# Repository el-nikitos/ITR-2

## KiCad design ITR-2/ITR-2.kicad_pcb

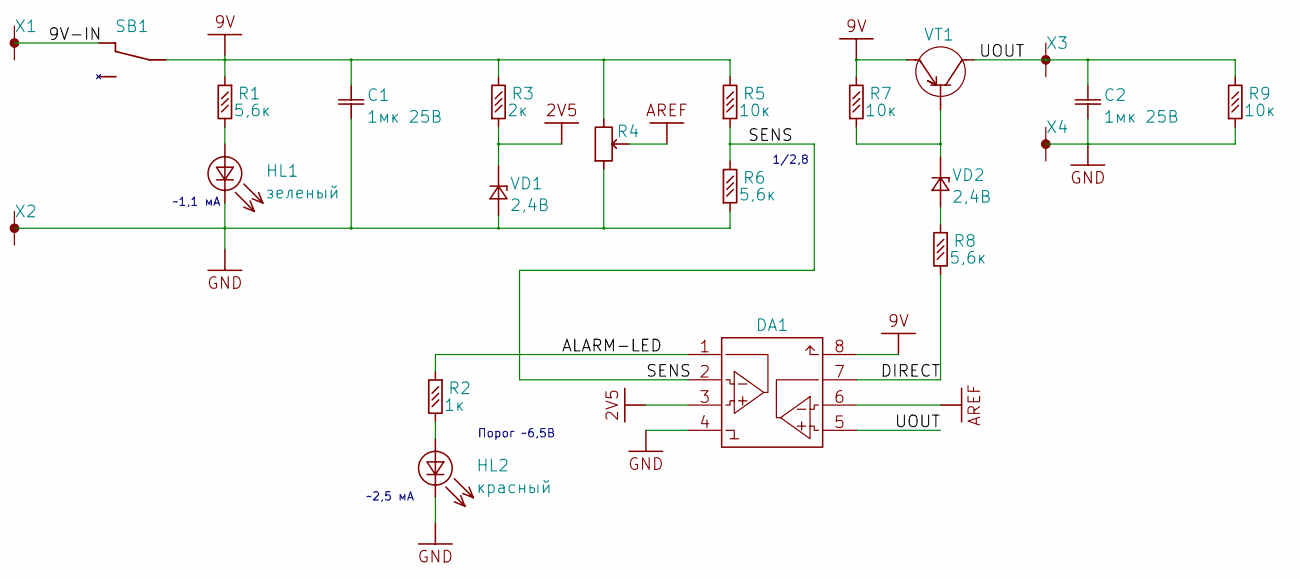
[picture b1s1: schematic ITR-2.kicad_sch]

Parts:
C1, C2: smd-конденсатор-керамика*0,01мк*25В*0603*ВП; Конденсатор_SMD_IEC_0603
DA1: ОУ*сдвоенный*so-8*ОТК; SO-8
HL1: smd-светодиод*зеленый*10мА*0603*ВП; Светодиод_SMD_IEC_0603(AK)
HL2: smd-светодиод*красный*10мА*0603*ВП; Светодиод_SMD_IEC_0603(AK)
R1, R2, R8: smd-резистор*4,7к*0603*ВП; Резистор_SMD_IEC_0603-0,1_Вт
R3, R5, R6, R7, R9: smd-резистор*10к*0,1Вт*5проц*0603*ВП; Резистор_SMD_IEC_0603-0,1_Вт
R4: DIP-переменный_резистор_R1001N12B1-A10K_вертикаль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; R1001N12B1-A10K-vertical
SB1: DIP-переключатель_KLS7-SS-12F19-G5; KLS7-SS-12F19-G5
VD1, VD2: smd-стабилитрон*6,8В*5мА*КД-36*ОТК; Корпус_IEC_КД-36
VT1: smd-транзистор*pnp*0,5А*50В*КТ-46*ОТК; Корпус_КТ-46
X1, X2, X3, X4: ico*группа_монтажных_отв.&1шт_1.2мм; Отверстие_под_пайку_D1.2

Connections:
2V5: DA1.3, R3.1, VD1.K
9V: C1.2, DA1.8, R1.1, R3.2, R4.3, R5.2, R7.2, SB1.2, VT1.2
/9V-IN: SB1.1, X1.1
/ALARM-LED: DA1.1, R2.1
/DIRECT: DA1.7, R8.2
/SENS: DA1.2, R5.1, R6.2
/UOUT: C2.2, DA1.5, R9.2, VT1.3, X3.1
AREF: DA1.6, R4.2
GND: C1.1, C2.1, DA1.4, HL1.K, HL2.K, R4.1, R6.1, R9.1, VD1.A, X2.1, X4.1
unnamed: HL1.A, R1.2
unnamed: HL2.A, R2.2
unnamed: R7.1, VD2.K, VT1.1
unnamed: R8.1, VD2.A

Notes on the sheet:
1/2,8
~2,5 мА
~1,1 мА
Порог ~6,5В

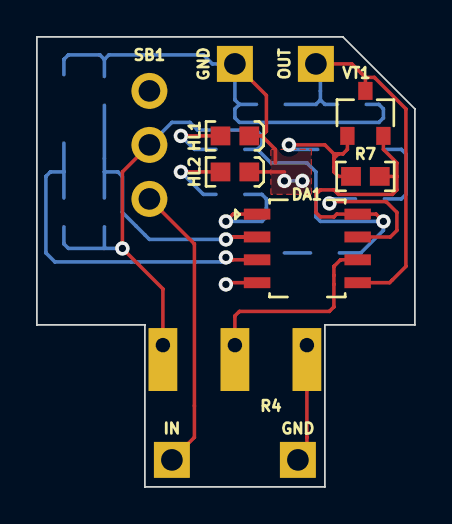
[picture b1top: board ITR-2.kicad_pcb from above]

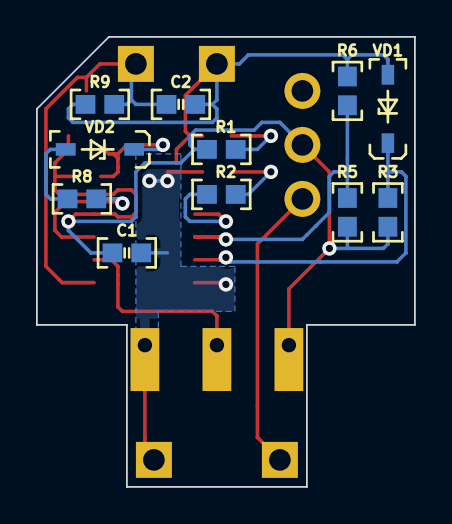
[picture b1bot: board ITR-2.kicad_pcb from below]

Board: 2 copper layers, 21.0 x 25.0 mm, 22 parts (11 on the bottom side), 13 nets.

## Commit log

2022-02-27 ковер с подогревом и подсветкой
2023-03-29 проект платы 20х14,5
2023-04-08 Т-образная плата с повторителем и контроле напряжения на ОУ
2023-04-08 гитигнор
2023-04-11 GBR для заказа
2023-05-02 исправления по результатам заказа: подтяжки на VT и Uout
2024-09-22 инициирована подготовка КД (СПСБ и производственных файлов)
2024-09-24 корпус - крайняя модель
